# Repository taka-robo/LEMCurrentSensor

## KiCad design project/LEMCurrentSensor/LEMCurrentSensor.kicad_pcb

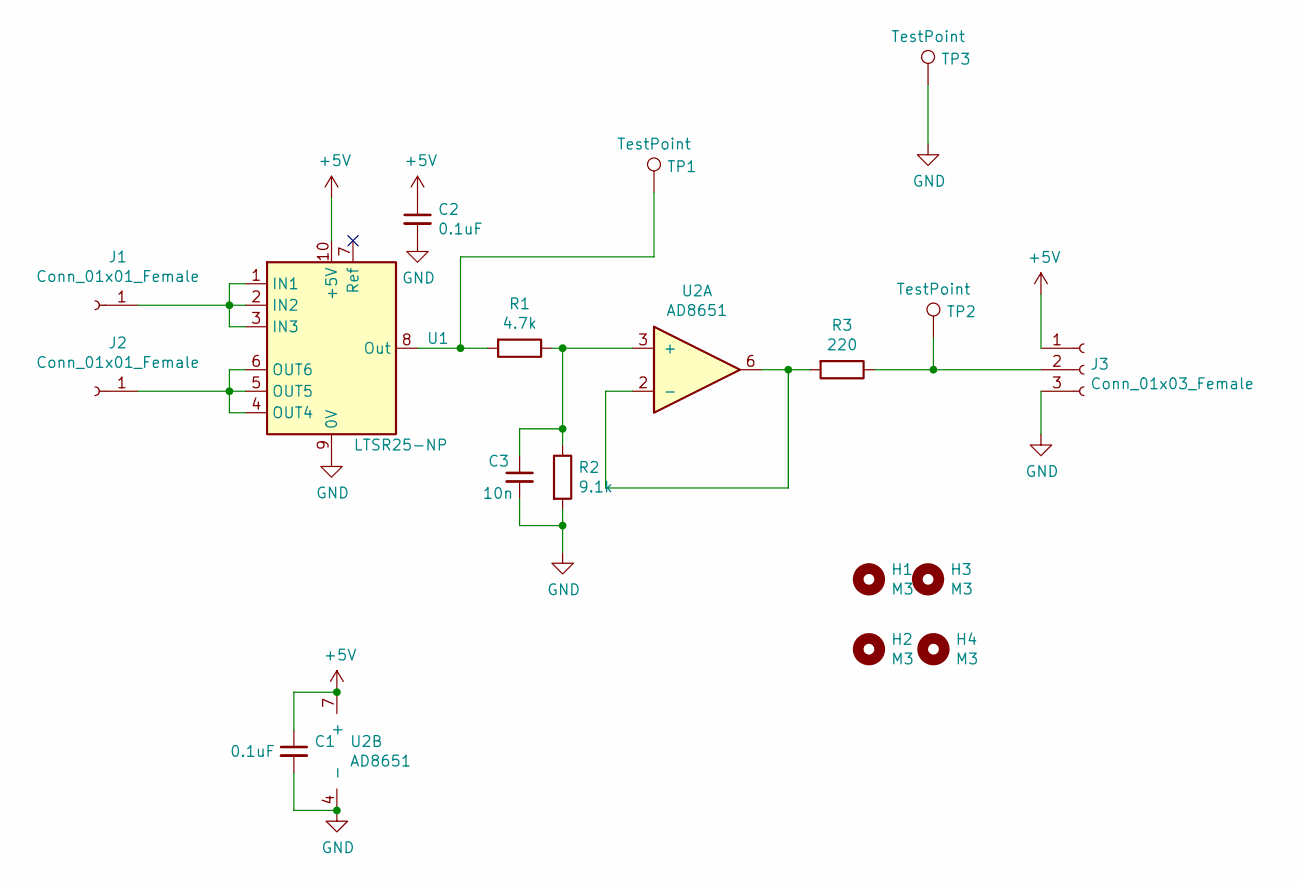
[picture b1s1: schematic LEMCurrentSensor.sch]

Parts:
C1, C2: 0.1uF; C_0603_1608Metric_Pad1.08x0.95mm_HandSolder
C3: 10n; C_0603_1608Metric_Pad1.08x0.95mm_HandSolder
H1, H2, H3, H4: M3; MountingHole_3.2mm_M3
J1, J2: Conn_01x01_Female; TestPoint_Pad_4.0x4.0mm
J3: Conn_01x03_Female; PinHeader_1x03_P2.54mm_Vertical
R1: 4.7k; R_0603_1608Metric_Pad0.98x0.95mm_HandSolder
R2: 9.1k; R_0603_1608Metric_Pad0.98x0.95mm_HandSolder
R3: 220; R_0603_1608Metric_Pad0.98x0.95mm_HandSolder
TP1, TP2, TP3: TestPoint; Pin_D0.7mm_L6.5mm_W1.8mm_FlatFork
U1: LTSR25-NP; LEM_LTSR-NP
U2: AD8651; SOIC-8_3.9x4.9mm_P1.27mm

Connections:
+5V: C1.1, C2.1, J3.1, U1.10 (+5V), U2.7 (+)
GND: C1.2, C2.2, C3.2, J3.3, R2.2, TP3.1, U1.9 (0V), U2.4 (-)
unnamed: C3.1, R1.1, R2.1, U2.3 (+)
unnamed: J1.1, U1.1 (IN1), U1.2 (IN2), U1.3 (IN3)
unnamed: J2.1, U1.4 (OUT4), U1.5 (OUT5), U1.6 (OUT6)
unnamed: J3.2, R3.1, TP2.1
unnamed: R1.2, TP1.1, U1.8 (Out)
unnamed: R3.2, U2.2 (-), U2.6

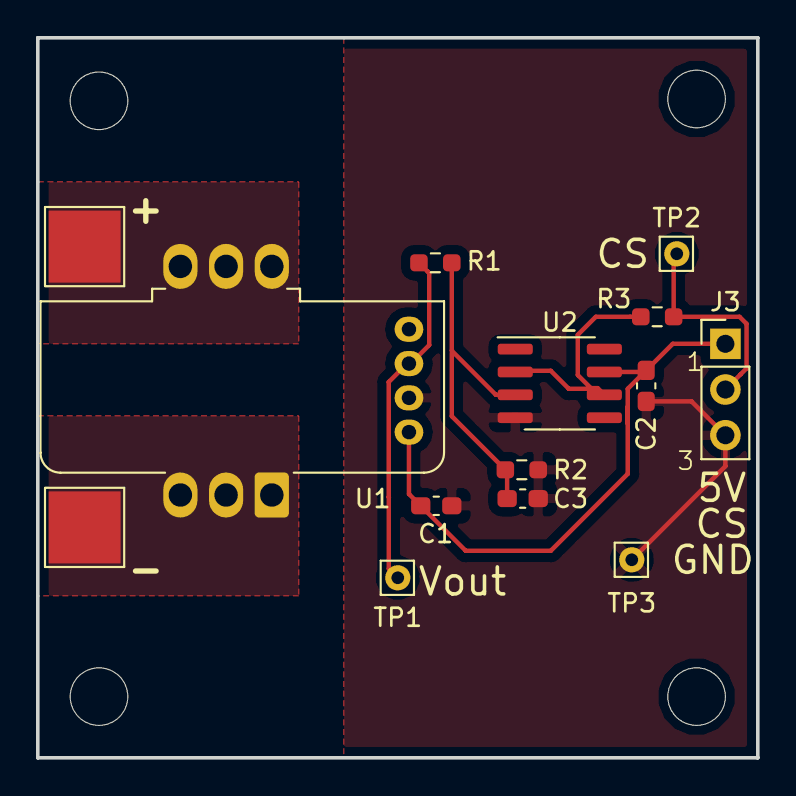
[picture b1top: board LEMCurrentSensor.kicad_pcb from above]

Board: 2 copper layers, 40.0 x 40.0 mm, 18 parts (0 on the bottom side), 8 nets.

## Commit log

2021-01-16 ver1.0
2021-01-16 発注用データ作成
2021-01-16 update ignore
